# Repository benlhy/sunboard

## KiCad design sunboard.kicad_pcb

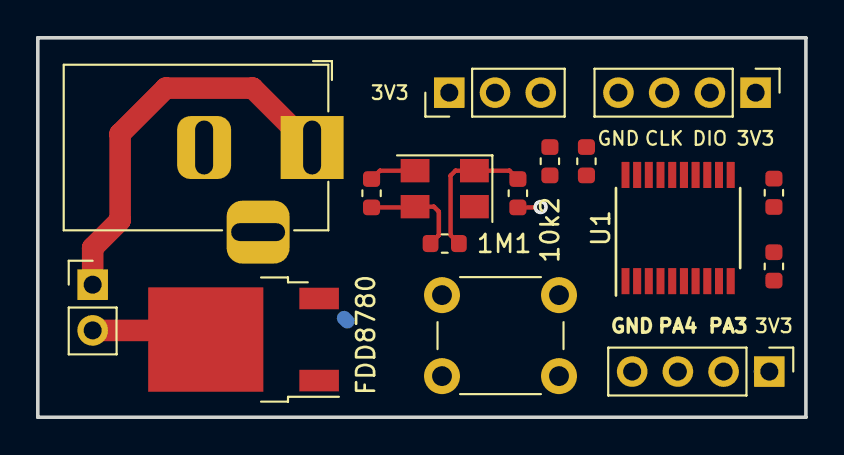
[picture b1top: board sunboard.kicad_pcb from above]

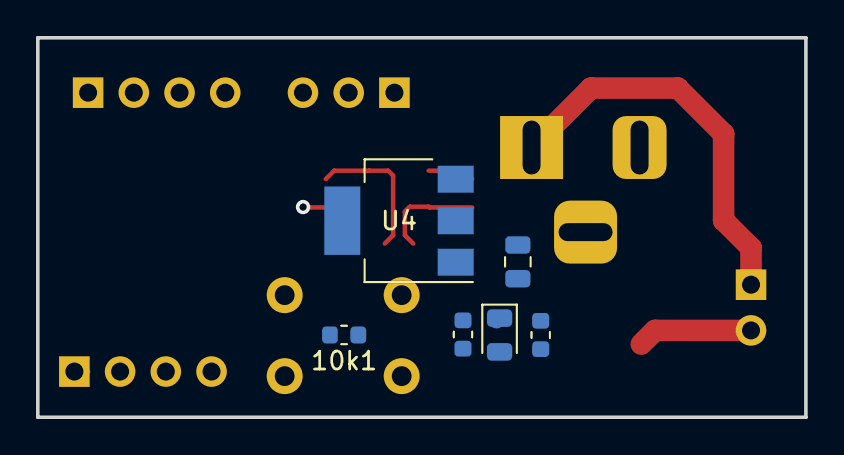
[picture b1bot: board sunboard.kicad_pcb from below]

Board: 2 copper layers, 42.7 x 21.1 mm, 22 parts (6 on the bottom side), 15 nets.

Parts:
0.1uF1: C; C_0805_2012Metric
0.1uF2, 0.1uF3, 0.1uF4, 0.1uF5, 20pF1, 20pF2: C; C_0603_1608Metric
1M1, 1k1, 10k1, 10k2: R; R_0603_1608Metric
BOOT0_SELECTOR1: Conn_01x03; PinHeader_1x03_P2.54mm_Vertical
FDD8780: Q_NMOS_GDS; TO-252-2
J1, J4: Conn_01x04; PinHeader_1x04_P2.54mm_Vertical
J2: Conn_01x02; PinHeader_1x02_P2.54mm_Vertical
J3: Barrel_Jack; BarrelJack_Horizontal
PWR_LED1: LED; LED_0805_2012Metric
SW1: SW_Push; SW_PUSH_6mm
U1: STM32F030F4Px; TSSOP-20_4.4x6.5mm_P0.65mm
U4: MIC5209; SOT-223
Y1: Crystal_Small; Crystal_SMD_5032-4Pin_5.0x3.2mm

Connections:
+3V3: 0.1uF2.1, 0.1uF3.1, 0.1uF4.1, 10k1.1, BOOT0_SELECTOR1.1, J1.1, J4.1, PWR_LED1.2, U1.5, U1.16, U4.3
+12V: 0.1uF1.1, J2.1, J3.1, U4.1
/BOOT0: 10k2.2, U1.1
/LED_GND: FDD8780.2, J2.2
/PA3: J4.2, U1.9
/PA4: J4.3, U1.10
/PWM: FDD8780.1, U1.17
/RESET: 0.1uF5.1, 10k1.2, SW1.2, U1.4
/SWCLK: J1.3, U1.20
/SWDIO: J1.2, U1.19
GND: 0.1uF1.2, 0.1uF2.2, 0.1uF3.2, 0.1uF4.2, 0.1uF5.2, 1k1.2, 20pF1.2, 20pF2.2, BOOT0_SELECTOR1.3, FDD8780.3, J1.4, J3.2, J4.4, SW1.1, U1.15, U4.2, U4.4, Y1.2, Y1.4
unnamed: 1M1.1, 20pF1.1, U1.2, Y1.1
unnamed: 1M1.2, 20pF2.1, U1.3, Y1.3
unnamed: 1k1.1, PWR_LED1.1
unnamed: 10k2.1, BOOT0_SELECTOR1.2

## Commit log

2019-01-31 fixed footprints
2019-01-31 some placement
2019-02-01 routed everything and added programming headers
2019-02-01 added extra header for two GPIOs
2019-02-02 added 3d models for the crystals
2019-02-17 Fixed programming header. Fixed order of header
2019-02-17 Fixed schematic
2019-02-17 init change lc branch
2019-02-17 updated sch and pcb
